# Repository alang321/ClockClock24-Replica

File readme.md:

# ClockClock 24 replica

Video of clock in action: https://photos.google.com/share/AF1QipM3veQpQ0XkVU6mXYjfI77cDL8gVcDZlROT0_qATZYPRnyIRZsuLHRsqtRsNTrixQ?key=c0U2SFBVdGpubVNTWW43WENBeFczdWVBSk5FbmZB

A clock consiting of 24 X40 stepper motors. There are 6 pcb where 4 of the X40 steppers are on a pcb. On each PCB 2 X40 (so 4 steppers, since X40 are dual axle) are controlled by a VID6606 stepper controller, so 2 VID6606 per PCB. These 2 are controlled by 1 MapleMini STM32F103. These 6 modules are controlled by a single RasberryPi Pico running MicroPython, this Pico communicates with the modules over I2C and also a DS3231 RTC for timekeeping. Additionally, as an optional addon a network model (a Pico W) can be added to get ITP time (This was added after everthing was finished so I didnt want to change the main control board to a Pico W). The clock works reliably with the newest addition of chekcsums and hasnt crashed since. Setting the time and display modes is done via a button panel of 4 buttons.

## Things to improve:
- The bus should be switched to CAN something else more robust then I2C, which is used here. I2C now works flawlessly for me but perhaps in a higher noise environment or over years errors would occur.
- Add pull down resistor for enable pin of vid 6606, connect to MCU pin (had to be botched in)
- Change microcontroller to smth cheaper/newer (RP2040?)
- Maybe switch to TMC2209 or smth for more silent driving (Some preliminary tests showed they do work with these steppers and are a bit more quiet, but they are much more expensive)

## Additional notes: 

- There was a plan to automatically zero the steppers with a small magnet and hall sensor but this was not implemented, but the sensor mountings are present on the PCB
- I lubricated the X40 steppers with SuperLube which did definitely reduce noise but this went back to normal levels after a few months.
- The main body is made of Korian which I had made by a professional using the drawing in the 3d parts folder
- Pointers where printed on a consumer FDM printer (Ender3V2) and where sanded and are friction fit.

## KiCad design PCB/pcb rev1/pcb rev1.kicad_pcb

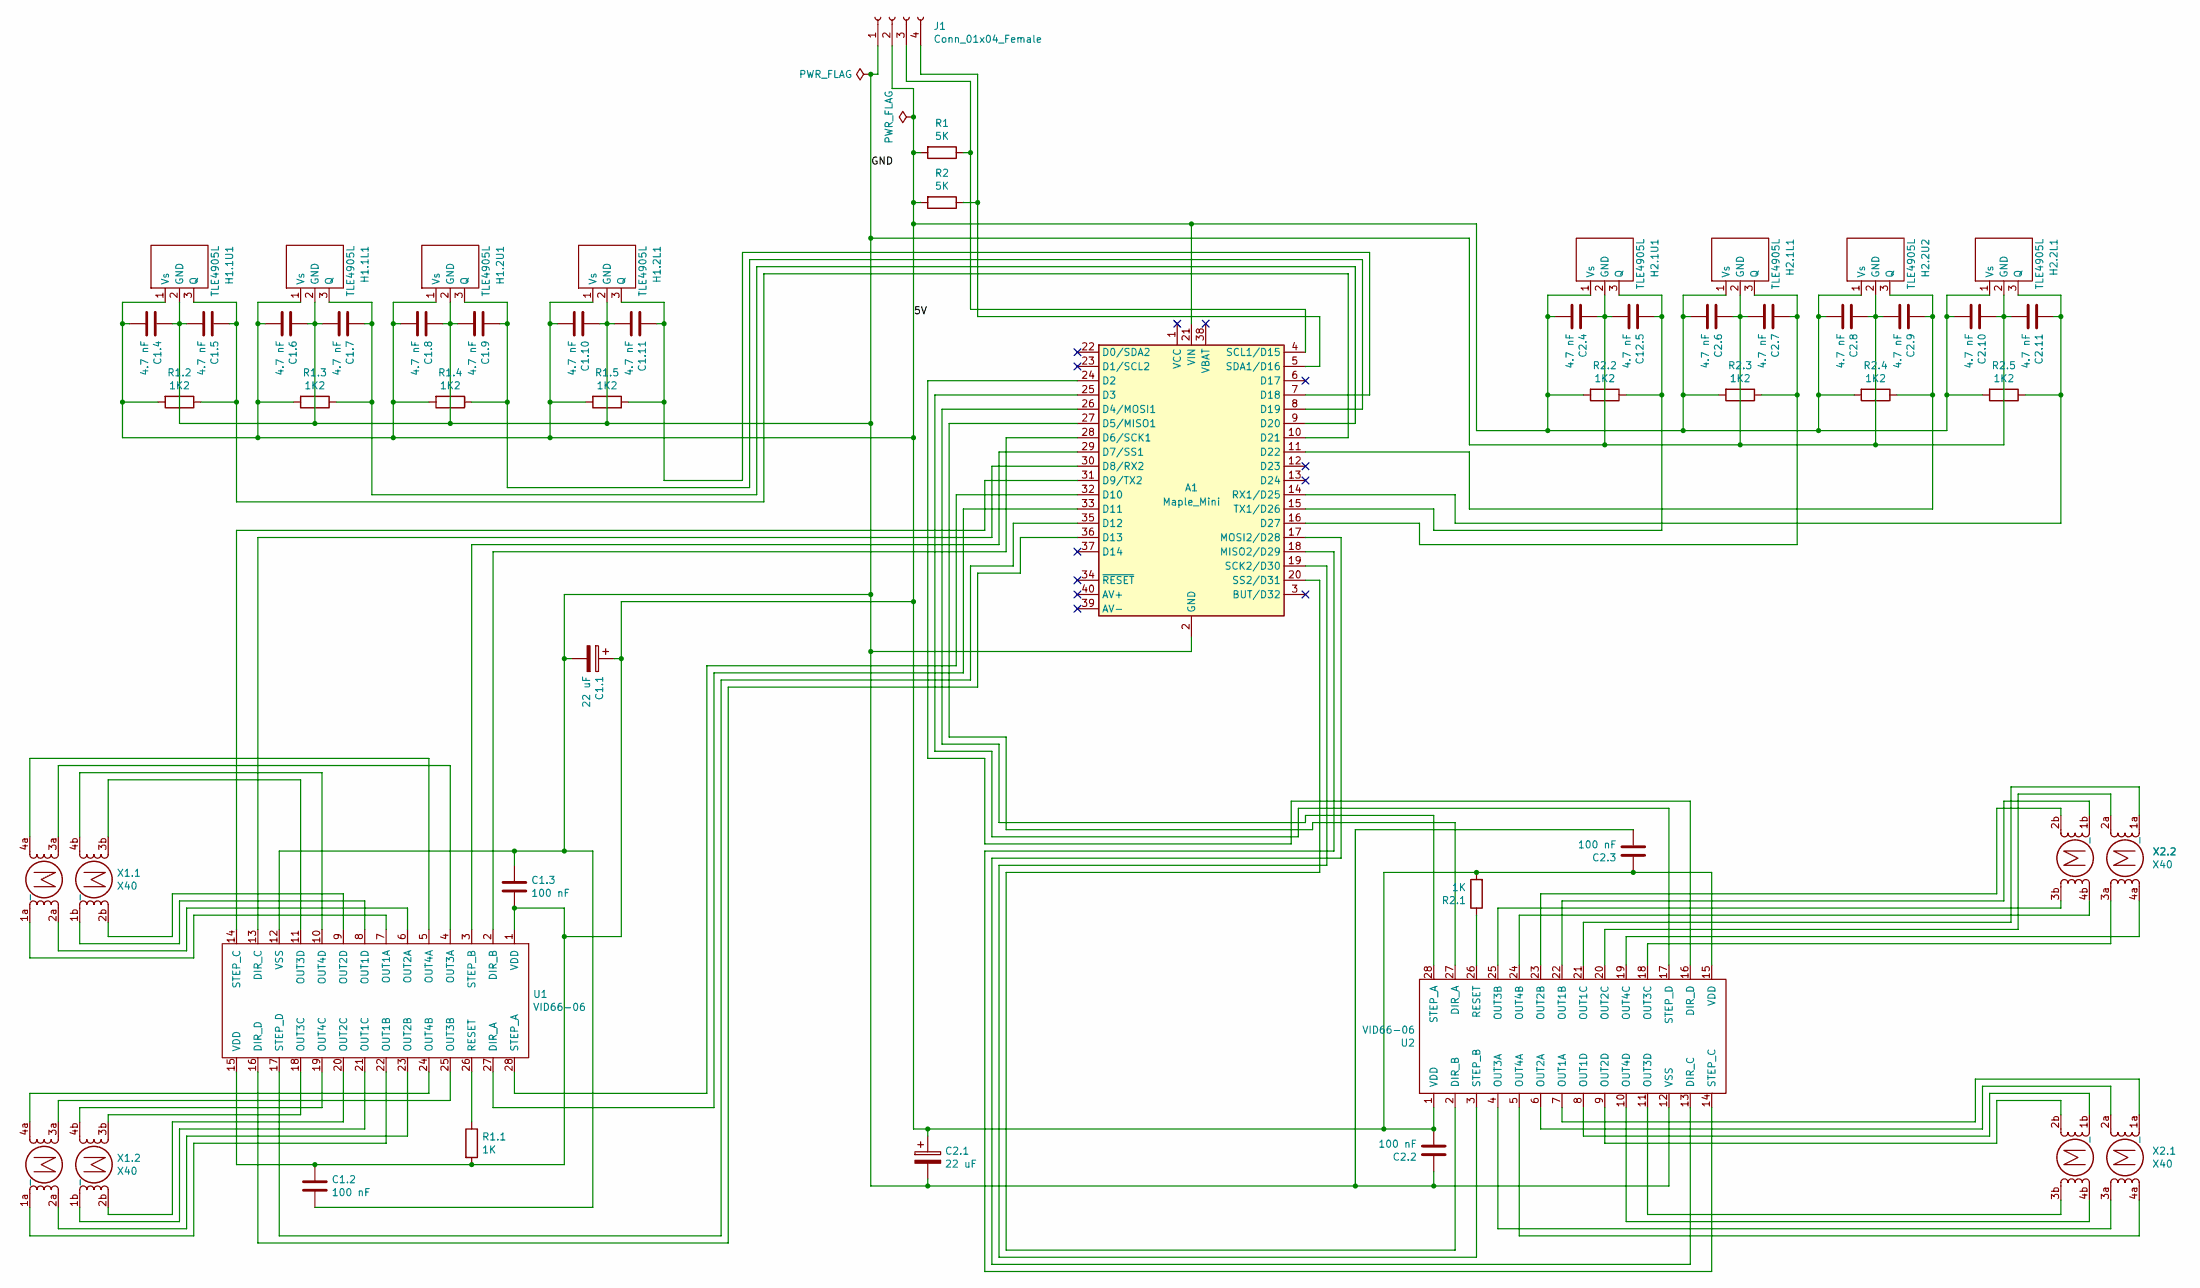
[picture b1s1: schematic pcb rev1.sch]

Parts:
A1: Maple_Mini
C1.1, C2.1: 22 uF; CP_Radial_D6.3mm_P2.50mm
C1.2, C1.3, C2.2, C2.3: 100 nF; C_Disc_D6.0mm_W2.5mm_P5.00mm
C1.4, C1.5, C1.6, C1.7, C1.8, C1.9, C1.10, C1.11, C2.4, C2.6, C2.7, C2.8, C2.9, C2.10, C2.11, C12.5: 4.7 nF; C_Disc_D6.0mm_W2.5mm_P5.00mm
H1.1L1, H1.1U1, H1.2L1, H1.2U1, H2.1L1, H2.1U1, H2.2L1, H2.2U2: TLE4905L; PG-SSO-3-02
J1: Conn_01x04_Female; PinHeader_1x04_P2.54mm_Vertical
R1, R2: 5K; R_Axial_DIN0207_L6.3mm_D2.5mm_P10.16mm_Horizontal
R1.1, R2.1: 1K; R_Axial_DIN0207_L6.3mm_D2.5mm_P10.16mm_Horizontal
R1.2, R1.3, R1.4, R1.5, R2.2, R2.3, R2.4, R2.5: 1K2; R_Axial_DIN0207_L6.3mm_D2.5mm_P10.16mm_Horizontal
U1, U2: VID66-06; SOP-28
X1.1, X1.2, X2.1, X2.2: X40

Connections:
/5V: A1.21 (VIN), C1.1.1, C1.2.1, C1.3.1, C1.4.1, C1.6.1, C1.8.1, C1.10.1, C2.1.1, C2.2.1, C2.3.1, C2.4.1, C2.6.1, C2.8.1, C2.10.1, H1.1L1.1 (Vs), H1.1U1.1 (Vs), H1.2L1.1 (Vs), H1.2U1.1 (Vs), H2.1L1.1 (Vs), H2.1U1.1 (Vs), H2.2L1.1 (Vs), H2.2U2.1 (Vs), J1.2, R1.2, R1.1.2, R1.2.2, R1.3.2, R1.4.2, R1.5.2, R2.2, R2.1.2, R2.2.2, R2.3.2, R2.4.2, R2.5.2, U1.1 (VDD), U1.15 (VDD), U2.1 (VDD), U2.15 (VDD)
/GND: A1.2 (GND), C1.1.2, C1.2.2, C1.3.2, C1.4.2, C1.5.1, C1.6.2, C1.7.1, C1.8.2, C1.9.1, C1.10.2, C1.11.1, C2.1.2, C2.2.2, C2.3.2, C2.4.2, C2.6.2, C2.7.1, C2.8.2, C2.9.1, C2.10.2, C2.11.1, C12.5.1, H1.1L1.2 (GND), H1.1U1.2 (GND), H1.2L1.2 (GND), H1.2U1.2 (GND), H2.1L1.2 (GND), H2.1U1.2 (GND), H2.2L1.2 (GND), H2.2U2.2 (GND), J1.1, U1.12 (VSS), U2.12 (VSS)
unnamed: A1.4 (SCL1/D15), J1.3, R1.1
unnamed: A1.5 (SDA1/D16), J1.4, R2.1
unnamed: A1.7 (D18), C1.11.2, H1.2L1.3 (Q), R1.5.1
unnamed: A1.8 (D19), C1.9.2, H1.2U1.3 (Q), R1.4.1
unnamed: A1.9 (D20), C1.7.2, H1.1L1.3 (Q), R1.3.1
unnamed: A1.10 (D21), C1.5.2, H1.1U1.3 (Q), R1.2.1
unnamed: A1.11 (D22), C2.9.2, H2.2U2.3 (Q), R2.4.1
unnamed: A1.14 (RX1/D25), C2.11.2, H2.2L1.3 (Q), R2.5.1
unnamed: A1.15 (TX1/D26), C12.5.2, H2.1U1.3 (Q), R2.2.1
unnamed: A1.16 (D27), C2.7.2, H2.1L1.3 (Q), R2.3.1
unnamed: A1.17 (MOSI2/D28), U2.13 (DIR_C)
unnamed: A1.18 (MISO2/D29), U2.14 (STEP_C)
unnamed: A1.19 (SCK2/D30), U2.3 (STEP_B)
unnamed: A1.20 (SS2/D31), U2.2 (DIR_B)
unnamed: A1.24 (D2), U2.16 (DIR_D)
unnamed: A1.25 (D3), U2.17 (STEP_D)
unnamed: A1.26 (D4/MOSI1), U2.28 (STEP_A)
unnamed: A1.27 (D5/MISO1), U2.27 (DIR_A)
unnamed: A1.28 (D6/SCK1), U1.2 (DIR_B)
unnamed: A1.29 (D7/SS1), U1.3 (STEP_B)
unnamed: A1.30 (D8/RX2), U1.13 (DIR_C)
unnamed: A1.31 (D9/TX2), U1.14 (STEP_C)
unnamed: A1.32 (D10), U1.28 (STEP_A)
unnamed: A1.33 (D11), U1.27 (DIR_A)
unnamed: A1.35 (D12), U1.17 (STEP_D)
unnamed: A1.36 (D13), U1.16 (DIR_D)
unnamed: R1.1.1, U1.26 (RESET)
unnamed: R2.1.1, U2.26 (RESET)
unnamed: U1.4 (OUT3A), X1.1.3a
unnamed: U1.5 (OUT4A), X1.1.4a
unnamed: U1.6 (OUT2A), X1.1.2a
unnamed: U1.7 (OUT1A), X1.1.1a (-)
unnamed: U1.8 (OUT1D), X1.1.1b (-)
unnamed: U1.9 (OUT2D), X1.1.2b
unnamed: U1.10 (OUT4D), X1.1.4b
unnamed: U1.11 (OUT3D), X1.1.3b
unnamed: U1.18 (OUT3C), X1.2.3b
unnamed: U1.19 (OUT4C), X1.2.4b
unnamed: U1.20 (OUT2C), X1.2.2b
unnamed: U1.21 (OUT1C), X1.2.1b (-)
unnamed: U1.22 (OUT1B), X1.2.1a (-)
unnamed: U1.23 (OUT2B), X1.2.2a
unnamed: U1.24 (OUT4B), X1.2.4a
unnamed: U1.25 (OUT3B), X1.2.3a
unnamed: U2.4 (OUT3A), X2.1.3a
unnamed: U2.5 (OUT4A), X2.1.4a
unnamed: U2.6 (OUT2A), X2.1.2a
unnamed: U2.7 (OUT1A), X2.1.1a (-)
unnamed: U2.8 (OUT1D), X2.1.1b (-)
unnamed: U2.9 (OUT2D), X2.1.2b
unnamed: U2.10 (OUT4D), X2.1.4b
unnamed: U2.11 (OUT3D), X2.1.3b
unnamed: U2.18 (OUT3C), X2.2.3a
unnamed: U2.19 (OUT4C), X2.2.4a
unnamed: U2.20 (OUT2C), X2.2.2a
unnamed: U2.21 (OUT1C), X2.2.1a (-)
unnamed: U2.22 (OUT1B), X2.2.1b (-)
unnamed: U2.23 (OUT2B), X2.2.2b
unnamed: U2.24 (OUT4B), X2.2.4b
unnamed: U2.25 (OUT3B), X2.2.3b

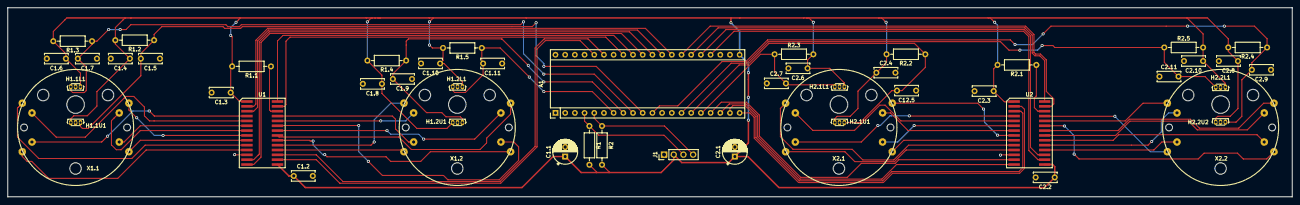
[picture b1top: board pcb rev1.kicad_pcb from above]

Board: 2 copper layers, 336.5 x 49.5 mm, 50 parts (0 on the bottom side), 62 nets.

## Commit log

2022-05-05 added submodules
2022-05-05 mini
2024-01-28 updated submodules and added some readme
2024-01-28 remove useless old pcb revs
